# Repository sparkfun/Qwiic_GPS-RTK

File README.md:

SparkFun Ublox GPS-RTK (Qwiic) - NEO-M8P-2
===========================================================

[*SparkFun GPS-RTK - NEO-M8P-2 (GPS-15005)*](https://www.sparkfun.com/products/15005)

The NEO-M8P-2 module is the top-of-the-line module for high accuracy GNSS and GPS location solutions including RTK. The NEO-M8P-2 is unique in that it is capable of both rover and base station operations. The ‘-2’ designation means this module has survey-in mode allowing the module to become a base station and produce RTCM 3.x correction data. 

Repository Contents
-------------------

* **/Documents** - Ublox datasheets and various whitepapers around RTK
* **/Hardware** - Eagle files

Documentation
--------------

* **[Installing an Arduino Library Guide](https://learn.sparkfun.com/tutorials/installing-an-arduino-library)** - Basic information on how to install an Arduino library.
* **[Arduino Library](https://github.com/sparkfun/SparkFun_u-blox_GNSS_Arduino_Library)** - Arduino Library for the SparkFun Ublox GPS-RTK.
* **[Hookup Guide](https://learn.sparkfun.com/tutorials/gps-rtk-hookup-guide)** - Basic hookup guide for the SparkFun Ublox GPS-RTK.

Product Versions
----------------
* [GPS-15005](https://www.sparkfun.com/products/15005) - SparkFun Red
* [SPX-14980](https://www.sparkfun.com/products/14980) - SparkX Black

License Information
-------------------

This product is _**open source**_! 

Various bits of the code have different licenses applied. Anything SparkFun wrote is beerware; if you see me (or any other SparkFun employee) at the local, and you've found our code helpful, please buy us a round!

Please use, reuse, and modify these files as you see fit. Please maintain attribution to SparkFun Electronics and release anything derivative under the same license.

Distributed as-is; no warranty is given.

- Your friends at SparkFun.

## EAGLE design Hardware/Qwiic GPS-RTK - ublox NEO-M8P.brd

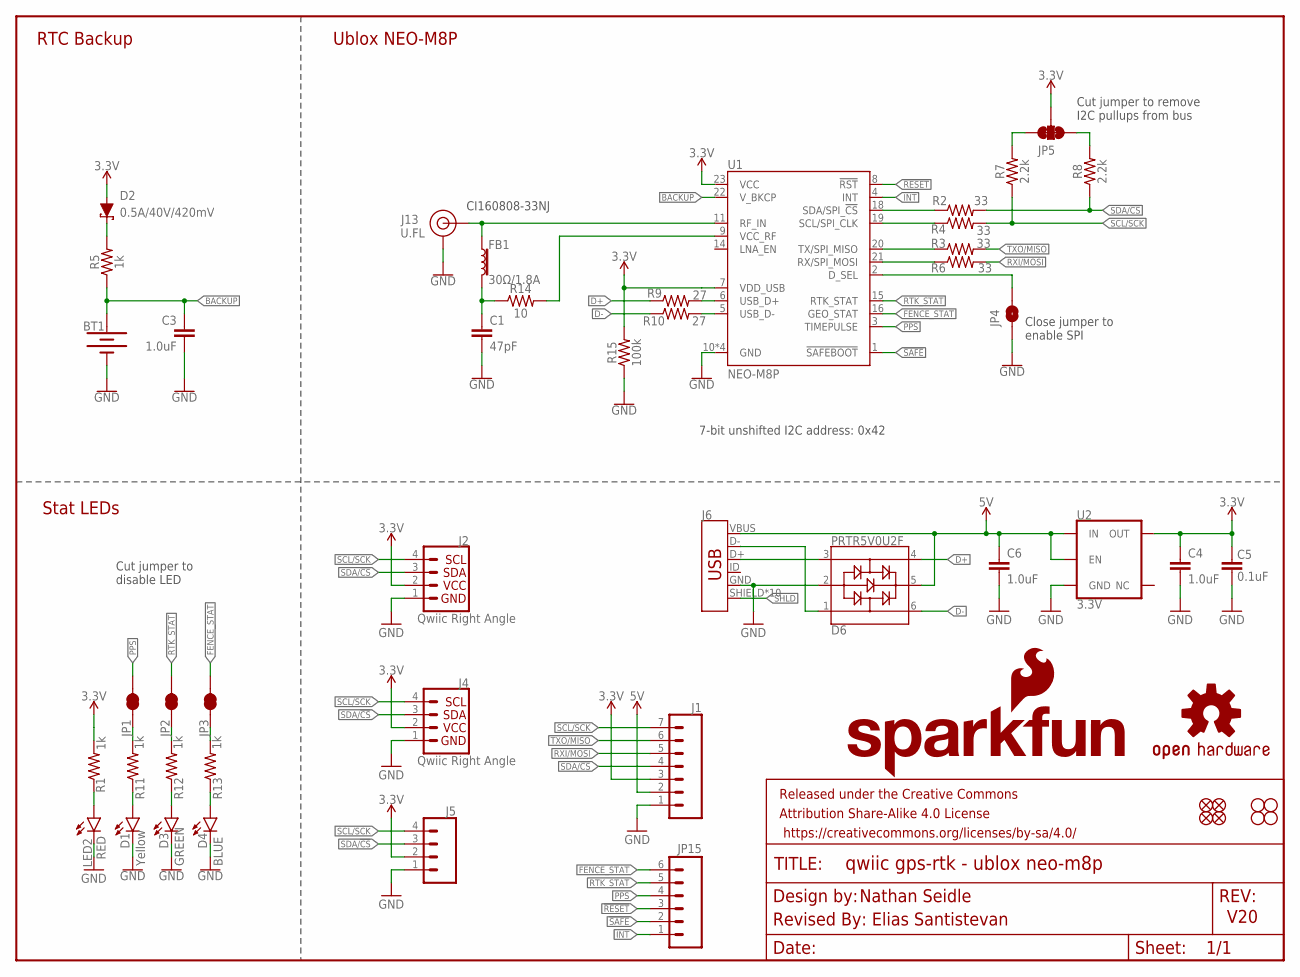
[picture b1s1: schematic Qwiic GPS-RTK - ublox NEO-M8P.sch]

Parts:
BT1: ML414H_IV01E_BATTERY; ML414H_IV01E
C1: 47pF; 0603
C3, C4, C6: 1.0uF; 0603
C5: 0.1uF; 0603
D1: Yellow; LED-0603
D2: 0.5A/40V/420mV; SOD-323
D3: GREEN; LED-0603
D4: BLUE; LED-0603
D6: PRTR5V0U2F; SOT886
FB1: 30Ω/1.8A; 0603
FRAME1: FRAME-LETTER; CREATIVE_COMMONS
J1: CONN_07NO_SILK; 1X07_NO_SILK
J2, J4: Qwiic Right Angle; JST04_1MM_RA
J5: CONN_041X04_NO_SILK; 1X04_NO_SILK
J6: USB_MICRO-B_HALF_PTH_MILL; USB-MICROB-PTH-MILL
J13: U.FL
JP1, JP2, JP3: JUMPER-SMT_2_NC_TRACE_SILK; SMT-JUMPER_2_NC_TRACE_SILK
JP4: JUMPER-SMT_2_NO_SILK; SMT-JUMPER_2_NO_SILK
JP5: JUMPER-SMT_3_2-NC_TRACE_SILK; SMT-JUMPER_3_2-NC_TRACE_SILK
JP15: M06NO_SILK_FEMALE_PTH; 1X06_NO_SILK
JP21, JP61, JP71, JP81: FIDUCIALUFIDUCIAL; FIDUCIAL-MICRO
JP31, JP41, JP91, JP101: STAND-OFFTIGHT; STAND-OFF-TIGHT
LED2: RED; LED-0603
LOGO1: OSHW-LOGOMINI; OSHW-LOGO-MINI
LOGO2: SFE_LOGO_NAME_FLAME.1_INCH; SFE_LOGO_NAME_FLAME_.1
R1, R5, R11, R12, R13: 1k; 0603
R2, R3, R4, R6: 33; 0603
R7, R8: 2.2k; 0603
R9, R10: 27; 0603
R14: 10; 0603
R15: 100k; 0603
U1: NEO-M8P
U2: 3.3V; SOT23-5

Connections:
3.3V: C4.1, C5.2, D2.A, J1.3, J2.2, J4.2, J5.2, JP5.2, R1.2, R15.2, U1.7 (VDD_USB), U1.23 (VCC), U2.5 (OUT)
5V: C6.1, D6.5, J1.2, J6.VBUS, U2.1 (IN), U2.3 (EN)
!RESET: JP15.3, U1.8 (!RST)
!SAFE: JP15.2, U1.1 (!SAFEBOOT!)
ANT_VCC: C1.1, FB1.2, R14.1
BACKUP: BT1.+, C3.1, R5.1, U1.22 (V_BKCP)
D+: D6.4, R9.1
D-: D6.6, R10.1
D_SEL: JP4.2, U1.2 (D_SEL)
FENCE_STAT: JP3.2, JP15.6, U1.16 (GEO_STAT)
GND: BT1.-, C1.2, C3.2, C4.2, C5.1, C6.2, D1.C, D3.C, D4.C, D6.2, J1.1, J2.1, J4.1, J5.1, J6.GND, J13.1 (GND), J13.2 (GND), JP4.1, LED2.C, R15.1, U1.10 (GND), U1.12 (GND), U1.13 (GND), U1.24 (GND), U2.2 (GND)
GPS_ANT1: FB1.1, J13.FEED (SIGNAL), U1.11 (RF_IN)
INT: JP15.1, U1.4 (INT)
unnamed: D3.A, R12.1
unnamed: D1.A, R11.1
unnamed: JP2.1, R12.2
unnamed: JP1.1, R11.2
unnamed: JP5.1, R8.2
unnamed: D2.C, R5.2
unnamed: D4.A, R13.1
unnamed: JP5.3, R7.2
unnamed: JP3.1, R13.2
unnamed: LED2.A, R1.1
unnamed: R9.2, U1.6 (USB_D+)
unnamed: R10.2, U1.5 (USB_D-)
unnamed: R14.2, U1.9 (VCC_RF)
PPS: JP1.2, JP15.4, U1.3 (TIMEPULSE)
RTK_STAT: JP2.2, JP15.5, U1.15 (RTK_STAT)
RXI/MOSI: J1.5, R6.2
RXLV: R6.1, U1.21 (RX/SPI_MOSI)
SCL/SCK: J1.7, J2.4, J4.4, J5.4, R4.2, R7.1
SCL_LV: R4.1, U1.19 (SCL/SPI_CLK)
SDA/!CS: J1.4, J2.3, J4.3, J5.3, R2.2, R8.1
SDA_LV: R2.1, U1.18 (SDA/SPI_!CS!)
SHLD: J6.SHIELD, J6.SHIELD2 (SHIELD), J6.SHIELD3 (SHIELD), J6.SHIELD4 (SHIELD), J6.SHIELD5 (SHIELD), J6.SHIELD6 (SHIELD), J6.SHIELD7 (SHIELD), J6.SHIELD8 (SHIELD), J6.SHIELD9 (SHIELD), J6.SHIELD10 (SHIELD)
TXLV: R3.1, U1.20 (TX/SPI_MISO)
TXO/MISO: J1.6, R3.2
USB_D+: D6.3, J6.D+
USB_D-: D6.1, J6.D-

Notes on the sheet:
V20
7-bit unshifted I2C address: 0x42
Ublox NEO-M8P
RTC Backup
Stat LEDs
Cut jumper to remove I2C pullups from bus
Cut jumper to disable LED
Close jumper to enable SPI
CI160808-33NJ
Nathan Seidle
Revised By: Elias Santistevan

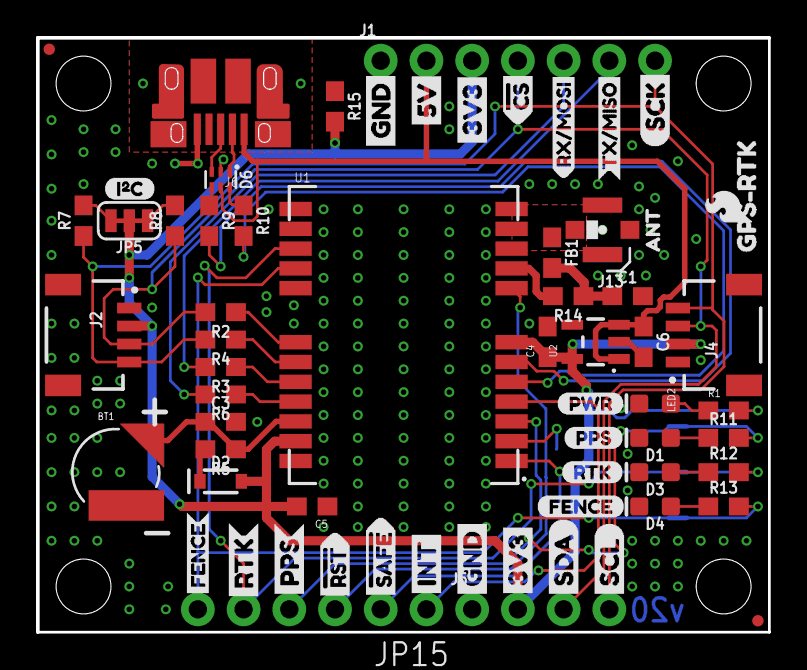
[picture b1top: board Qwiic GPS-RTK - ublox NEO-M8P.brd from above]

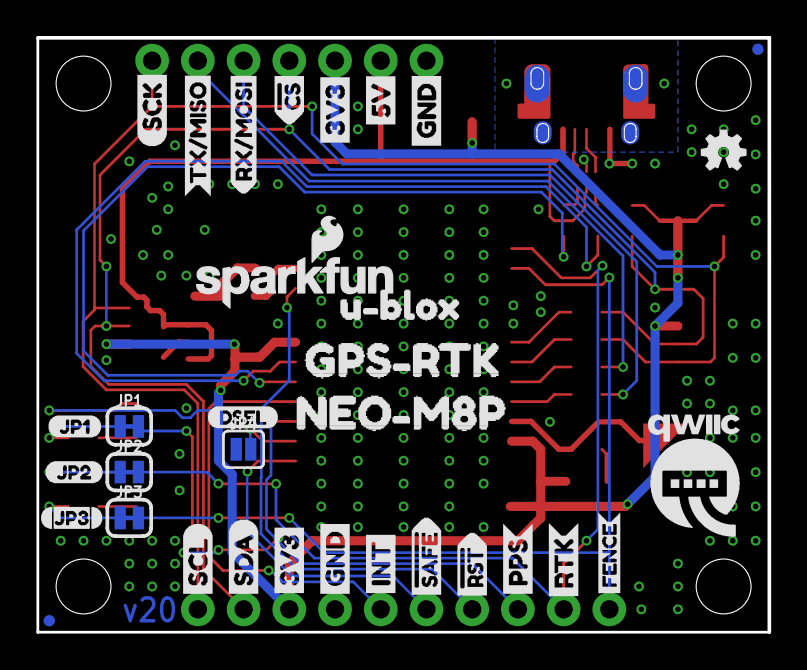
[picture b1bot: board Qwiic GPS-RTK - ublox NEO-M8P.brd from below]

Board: 2 copper layers, 40.6 x 33.0 mm, 103 parts (33 on the bottom side), 39 nets.

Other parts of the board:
U$1, U$4: SDA-[)
U$3, U$5: SCL-[)
U$6, U$7, U$60, U$61: 3V3-04
U$8, U$9, U$62, U$63: GND-04
U$10: I_SUPER2_C-()-03
U$11: FENCE2
U$12: JP20
U$13, U$28, U$29: RTK1
U$14, U$17: FENCE0
U$15, U$16: INT8
U$18: PWR-()-03
U$19, U$20: 5V
U$21: GPS#RTK0
U$22: U#BLOX3
U$23, U$24: CS#-<]
U$25: JP10
U$26: RX#MOSI2
U$27: DSEL0
U$30: QWIIC-LOGO-MEDIUM
U$31: RX#MOSI3
U$32: JP32
U$33: SFE_LOGO_FLAME_.1
U$34: TX#MISO0
U$35, U$36: #RST3
U$37: TX#MISO1
U$38, U$41: SCK-(]-04
U$39, U$40: #SAFE1
U$43, U$44: PPS5
U$52: PPS0
U$53: NEO#M8P3
U$54: GPS#RTK1
U$55: ANT0

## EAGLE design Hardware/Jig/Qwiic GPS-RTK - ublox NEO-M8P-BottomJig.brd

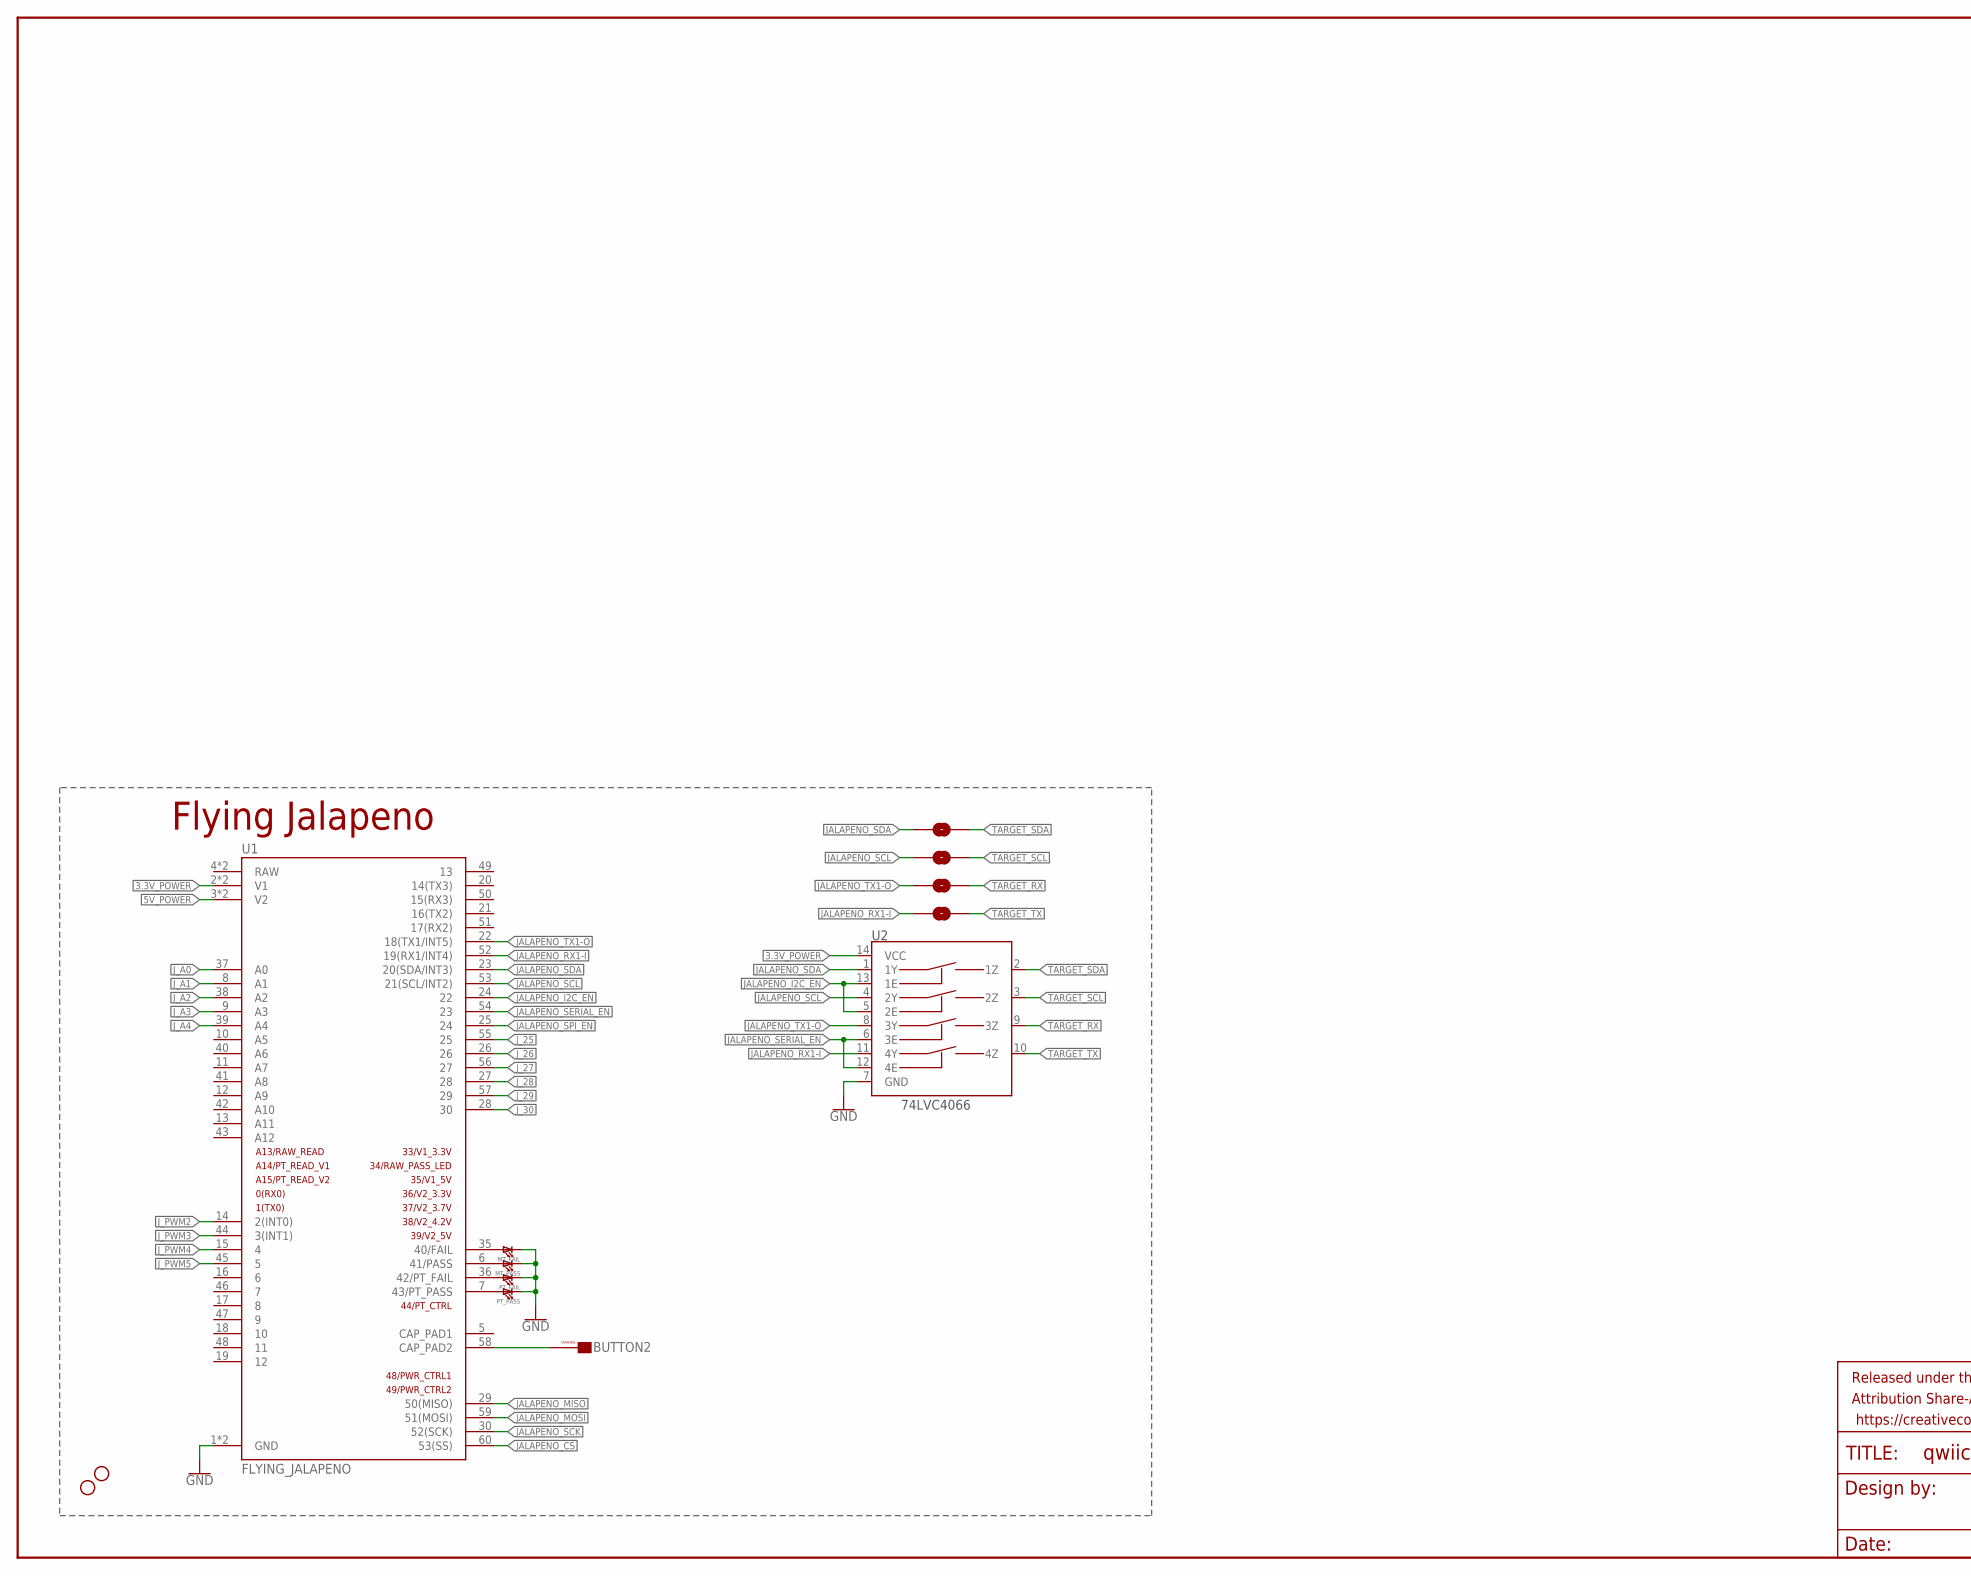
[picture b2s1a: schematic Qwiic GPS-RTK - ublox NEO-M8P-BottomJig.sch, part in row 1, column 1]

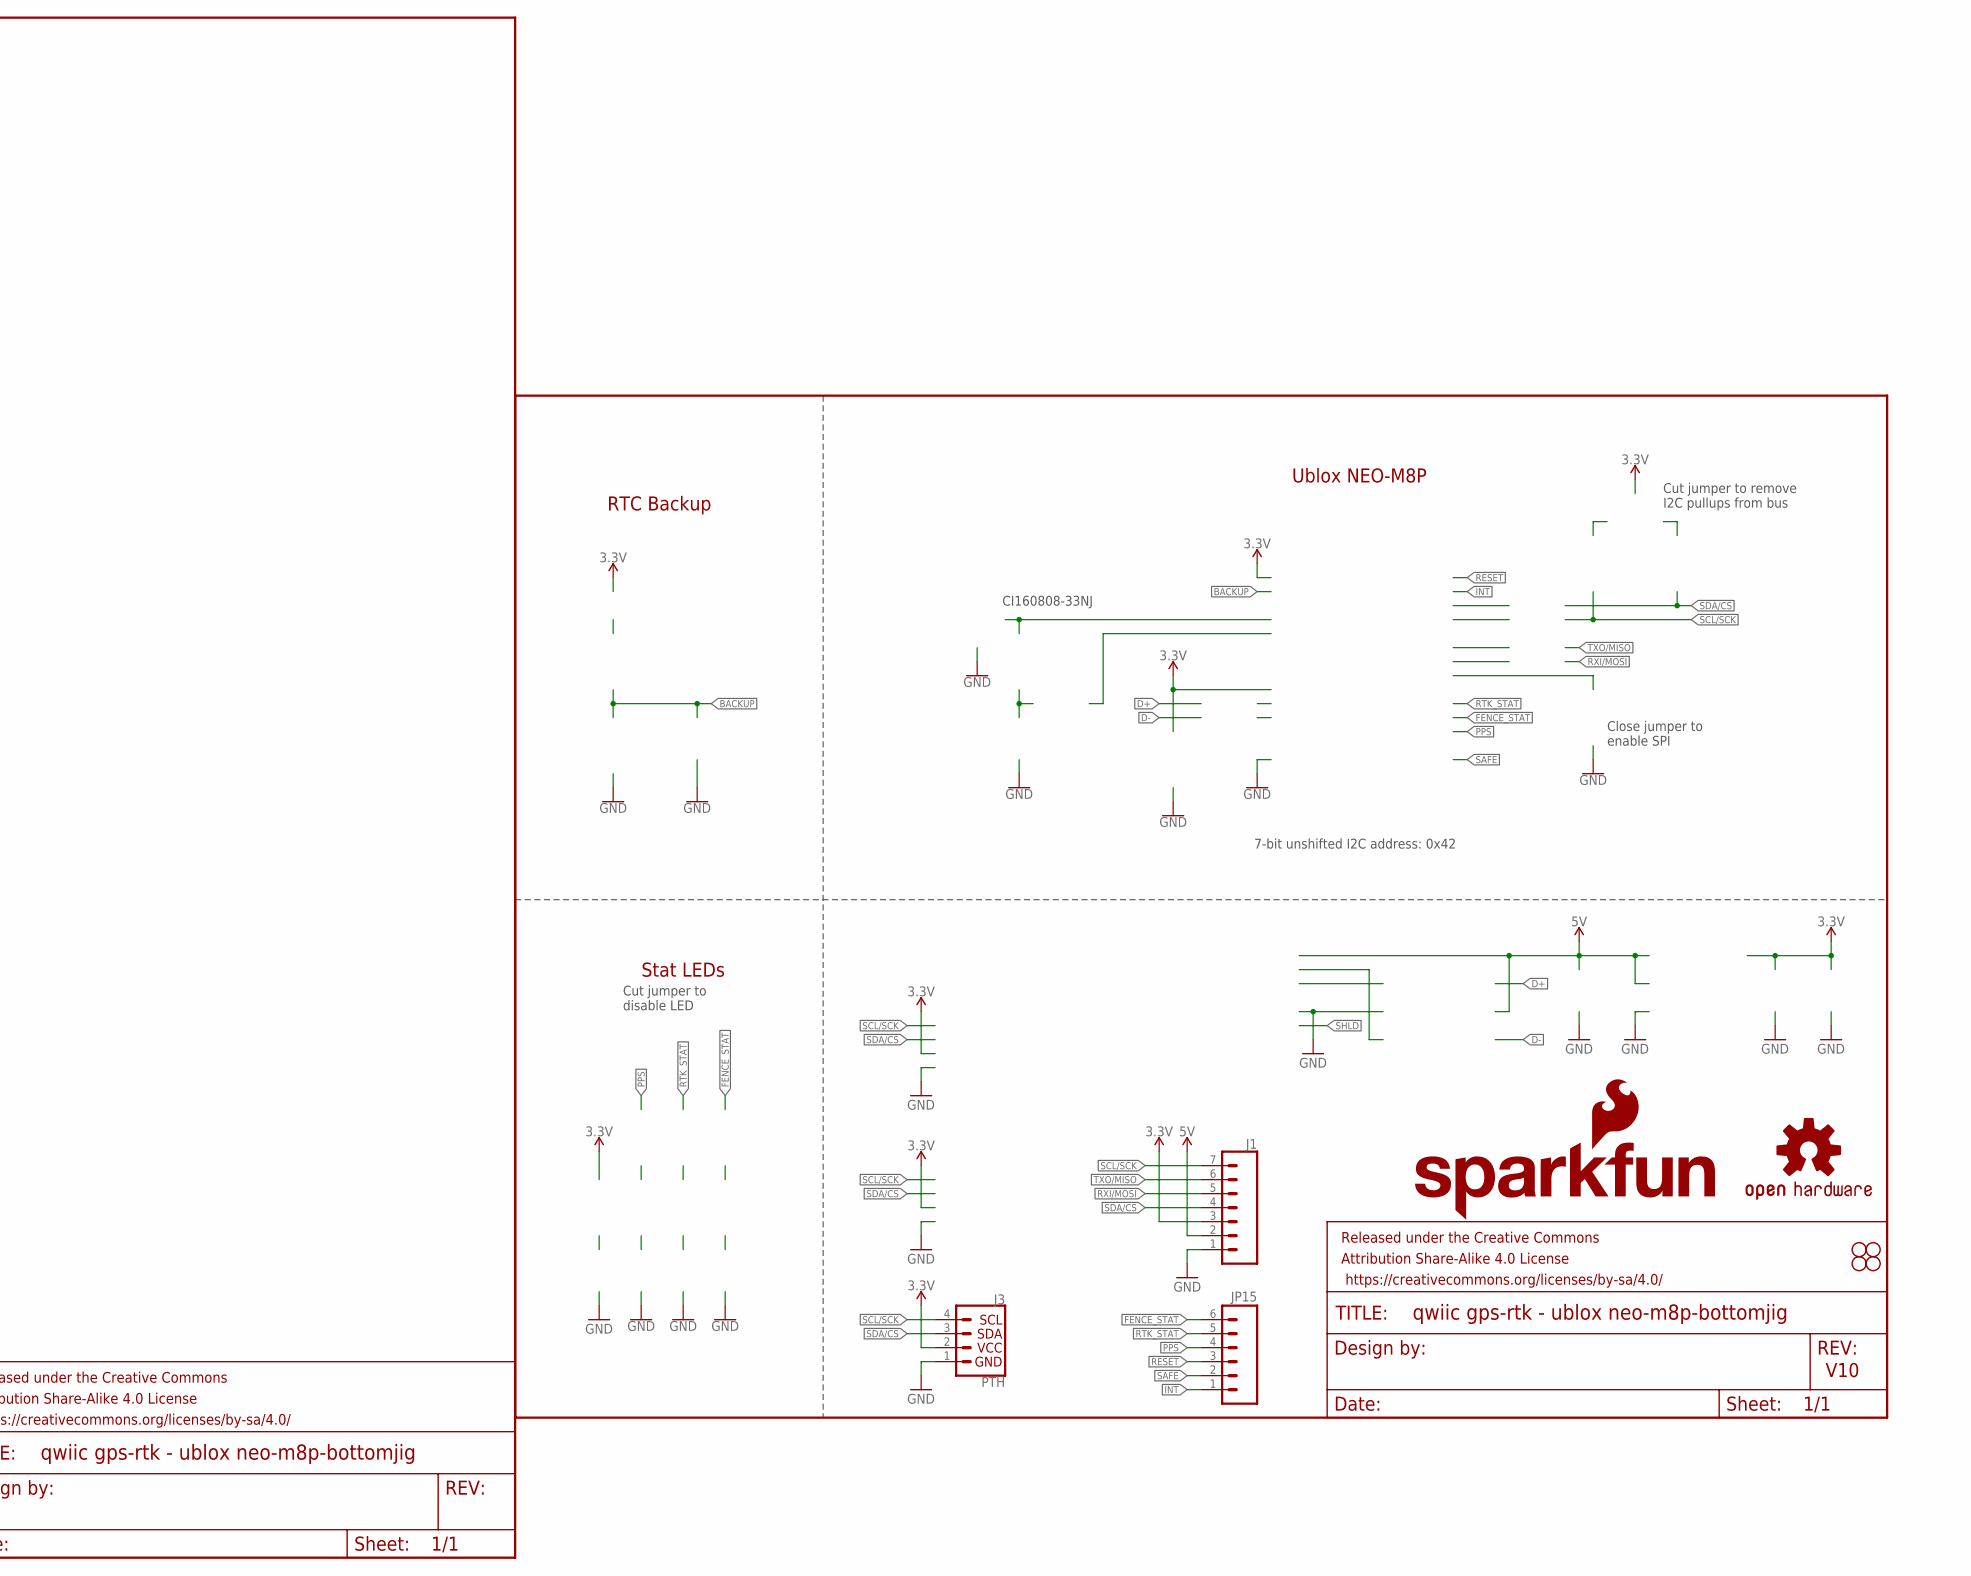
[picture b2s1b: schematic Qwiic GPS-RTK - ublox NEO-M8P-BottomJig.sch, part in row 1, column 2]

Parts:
BUTTON2: CAPSENSE_BUTTON_PAD_ONLY; CAPSENSE_BUTTON_PADS_ONLY
FRAME1: FRAME-LETTER; CREATIVE_COMMONS
FRAME2: FRAME-LEDGER; CREATIVE_COMMONS
H1, H3: STAND-OFF
J1: CONN_07NO_SILK; 1X07_NO_SILK
J3: PTH; 1X04_NO_SILK
JP15: M06NO_SILK_FEMALE_PTH; 1X06_NO_SILK
JP31, JP41, JP91, JP101: STAND-OFF
J_SCL, J_SCL1, J_SCL2: JUMPER-SMT_2_NO_NO-SILK; SMT-JUMPER_2_NO_NO-SILK
J_SDA: JUMPER-SMT_2_NO_NO-SILK; SMT-JUMPER_2_NO_NO-SILK
LOGO1: OSHW-LOGOMINI; OSHW-LOGO-MINI
LOGO2: SFE_LOGO_NAME_FLAME.1_INCH; SFE_LOGO_NAME_FLAME_.1
MT_FAIL: LED1206; LED-1206
MT_PASS: LED1206; LED-1206
PT_FAIL: LED1206; LED-1206
PT_PASS: LED1206; LED-1206
U1: FLYING_JALAPENO; FLYING_JALAPENO_V3_M
U2: 74LVC4066; SO14

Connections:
3.3V: J1.3, J3.2 (VCC)
3.3V_POWER: U1.2 (V1), U1.32 (V1), U2.14 (VCC)
5V: J1.2
5V_POWER: U1.3 (V2), U1.33 (V2)
!RESET: JP15.3
!SAFE: JP15.2
BUTTON2: BUTTON2.CAPSENSE_PAD, U1.58 (CAP_PAD2)
FENCE_STAT: JP15.6
GND: J1.1, J3.1 (GND), MT_FAIL.C, MT_PASS.C, PT_FAIL.C, PT_PASS.C, U1.1 (GND), U1.31 (GND), U2.7 (GND)
INT: JP15.1
JALAPENO_CS: U1.60 (53(SS))
JALAPENO_I2C_EN: U1.24 (22), U2.5 (2E), U2.13 (1E)
JALAPENO_MISO: U1.29 (50(MISO))
JALAPENO_MOSI: U1.59 (51(MOSI))
JALAPENO_RX1-I: J_SDA.1, U1.52 (19(RX1/INT4)), U2.11 (4Y)
JALAPENO_SCK: U1.30 (52(SCK))
JALAPENO_SCL: J_SCL.1, U1.53 (21(SCL/INT2)), U2.4 (2Y)
JALAPENO_SDA: J_SCL2.1, U1.23 (20(SDA/INT3)), U2.1 (1Y)
JALAPENO_SERIAL_EN: U1.54 (23), U2.6 (3E), U2.12 (4E)
JALAPENO_SPI_EN: U1.25 (24)
JALAPENO_TX1-O: J_SCL1.1, U1.22 (18(TX1/INT5)), U2.8 (3Y)
J_25: U1.55 (25)
J_26: U1.26
J_27: U1.56 (27)
J_28: U1.27 (28)
J_29: U1.57 (29)
J_30: U1.28 (30)
J_A0: U1.37 (A0)
J_A1: U1.8 (A1)
J_A2: U1.38 (A2)
J_A3: U1.9 (A3)
J_A4: U1.39 (A4)
J_PWM2: U1.14 (2(INT0))
J_PWM3: U1.44 (3(INT1))
J_PWM4: U1.15 (4)
J_PWM5: U1.45 (5)
unnamed: PT_PASS.A, U1.7 (43/PT_PASS)
unnamed: PT_FAIL.A, U1.36 (42/PT_FAIL)
unnamed: MT_PASS.A, U1.6 (41/PASS)
unnamed: MT_FAIL.A, U1.35 (40/FAIL)
PPS: JP15.4
RTK_STAT: JP15.5
RXI/MOSI: J1.5
SCL/SCK: J1.7, J3.4 (SCL)
SDA/!CS: J1.4, J3.3 (SDA)
TARGET_RX: J_SCL1.2, U2.9 (3Z)
TARGET_SCL: J_SCL.2, U2.3 (2Z)
TARGET_SDA: J_SCL2.2, U2.2 (1Z)
TARGET_TX: J_SDA.2, U2.10 (4Z)
TXO/MISO: J1.6

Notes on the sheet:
V10
7-bit unshifted I2C address: 0x42
Ublox NEO-M8P
RTC Backup
Stat LEDs
Cut jumper to remove I2C pullups from bus
Cut jumper to disable LED
Close jumper to enable SPI
CI160808-33NJ
Flying Jalapeno

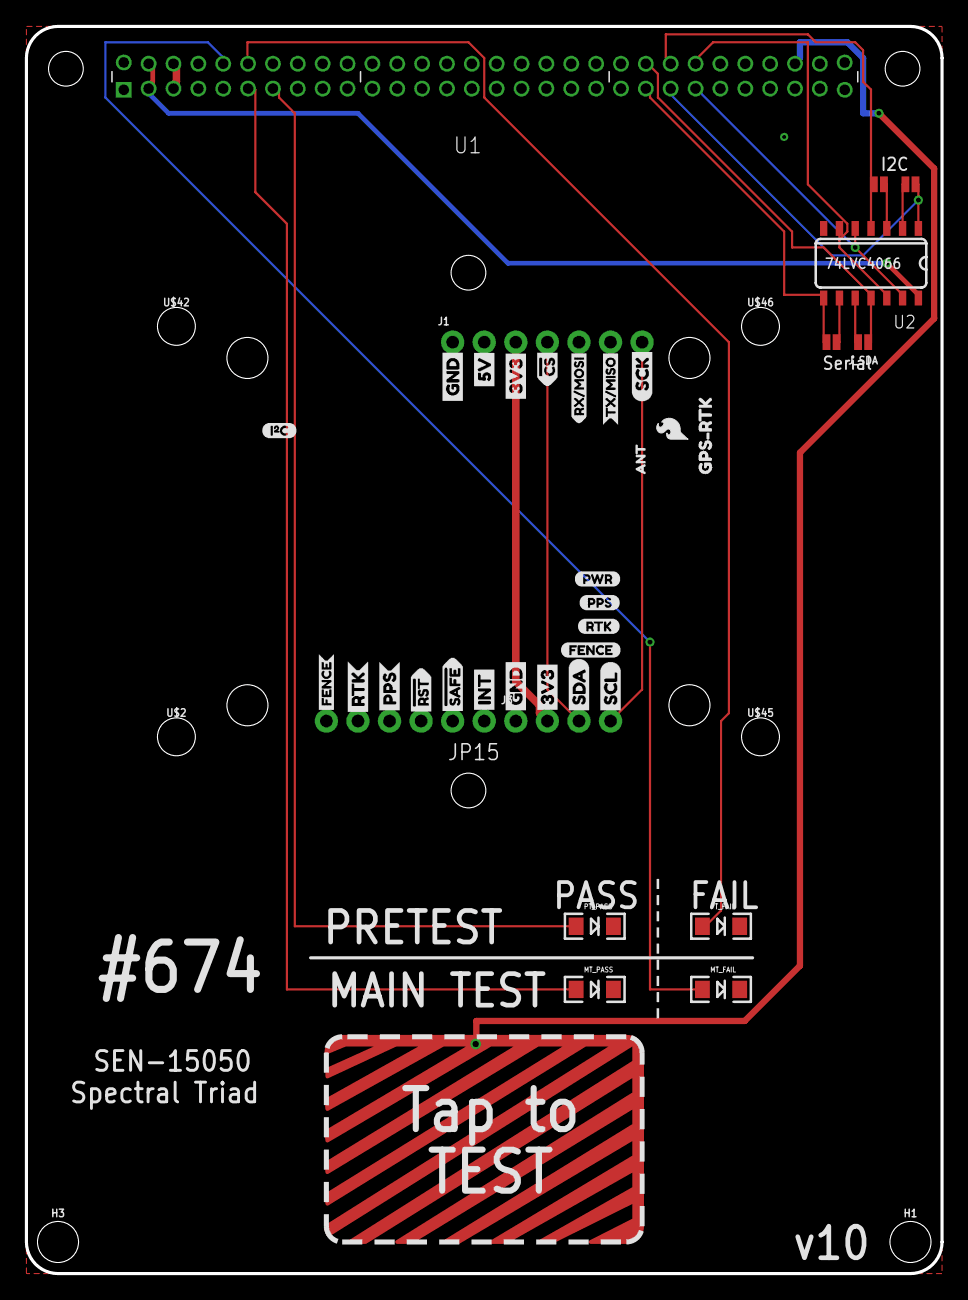
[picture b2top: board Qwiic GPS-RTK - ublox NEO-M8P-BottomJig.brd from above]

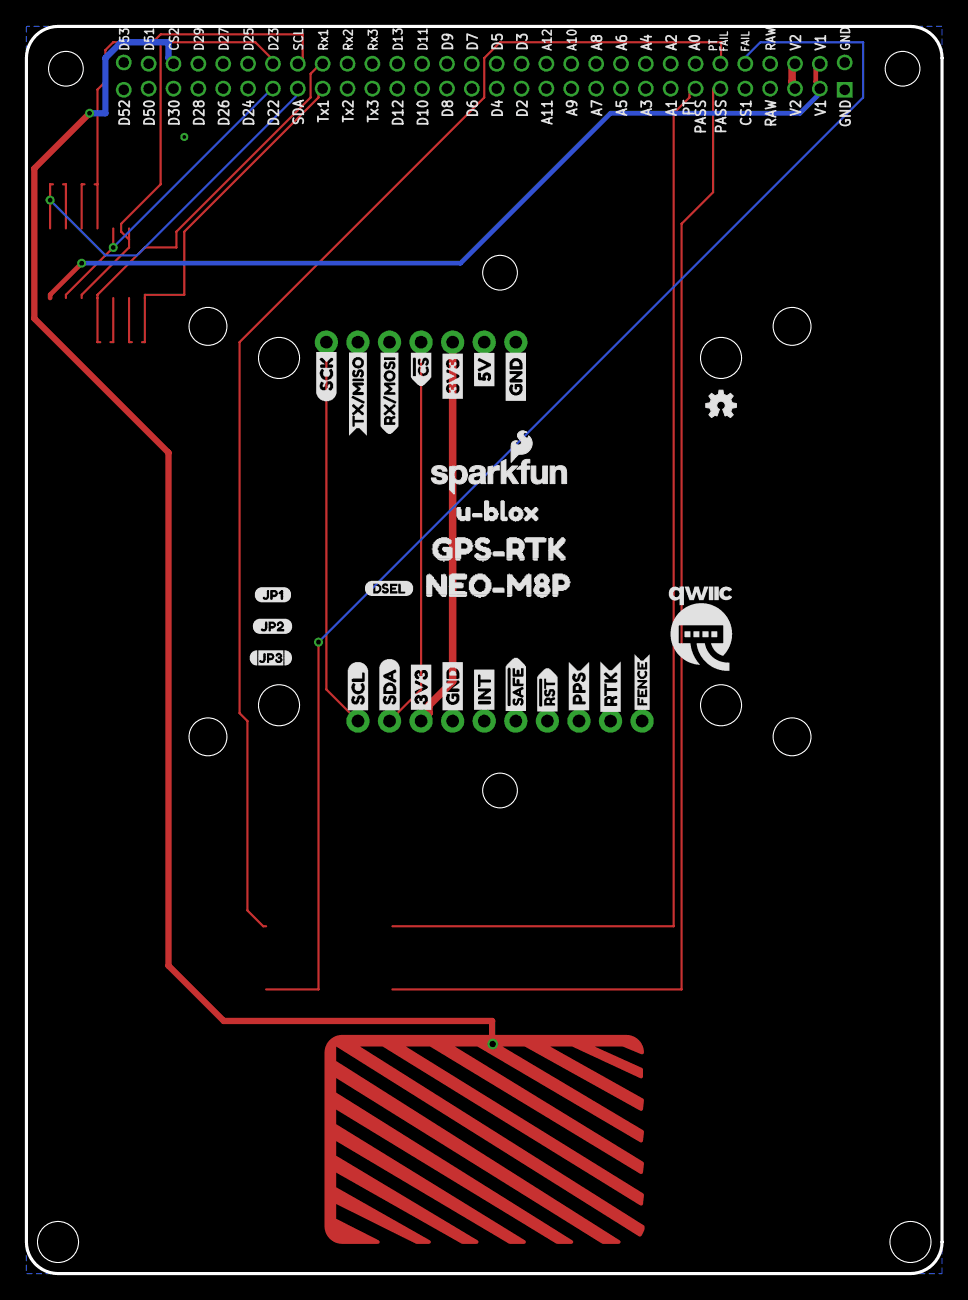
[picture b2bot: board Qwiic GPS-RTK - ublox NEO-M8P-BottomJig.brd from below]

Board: 2 copper layers, 73.7 x 100.3 mm, 80 parts (27 on the bottom side), 21 nets.

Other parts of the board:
U$1, U$4: SDA-[)
U$2, U$42, U$45, U$46: STAND-OFF-TIGHT
U$3, U$5: SCL-[)
U$6, U$7, U$60, U$61: 3V3-04
U$8, U$9, U$62, U$63: GND-04
U$10: I_SUPER2_C-()-03
U$11: FENCE2
U$12: JP20
U$13, U$28, U$29: RTK1
U$14, U$17: FENCE0
U$15, U$16: INT8
U$18: PWR-()-03
U$19, U$20: 5V
U$21: GPS#RTK0
U$22: U#BLOX3
U$23, U$24: CS#-<]
U$25: JP10
U$26: RX#MOSI2
U$27: DSEL0
U$30: QWIIC-LOGO-MEDIUM
U$31: RX#MOSI3
U$32: JP32
U$33: SFE_LOGO_FLAME_.1
U$34: TX#MISO0
U$35, U$36: #RST3
U$37: TX#MISO1
U$38, U$41: SCK-(]-04
U$39, U$40: #SAFE1
U$43, U$44: PPS5
U$47, U$48: NUBBIN_LOCKER
U$52: PPS0
U$53: NEO#M8P3
U$54: GPS#RTK1
U$55: ANT0

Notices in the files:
parts and their libraries:
SparkFun-Connectors: Licensing: Creative Commons ShareAlike 4.0 International - https://creativecommons.org/licenses/by-sa/4.0
SparkFun-Aesthetics: Released under the Creative Commons Attribution Share-Alike 4.0 License
SparkFun-Aesthetics: https://creativecommons.org/licenses/by-sa/4.0
